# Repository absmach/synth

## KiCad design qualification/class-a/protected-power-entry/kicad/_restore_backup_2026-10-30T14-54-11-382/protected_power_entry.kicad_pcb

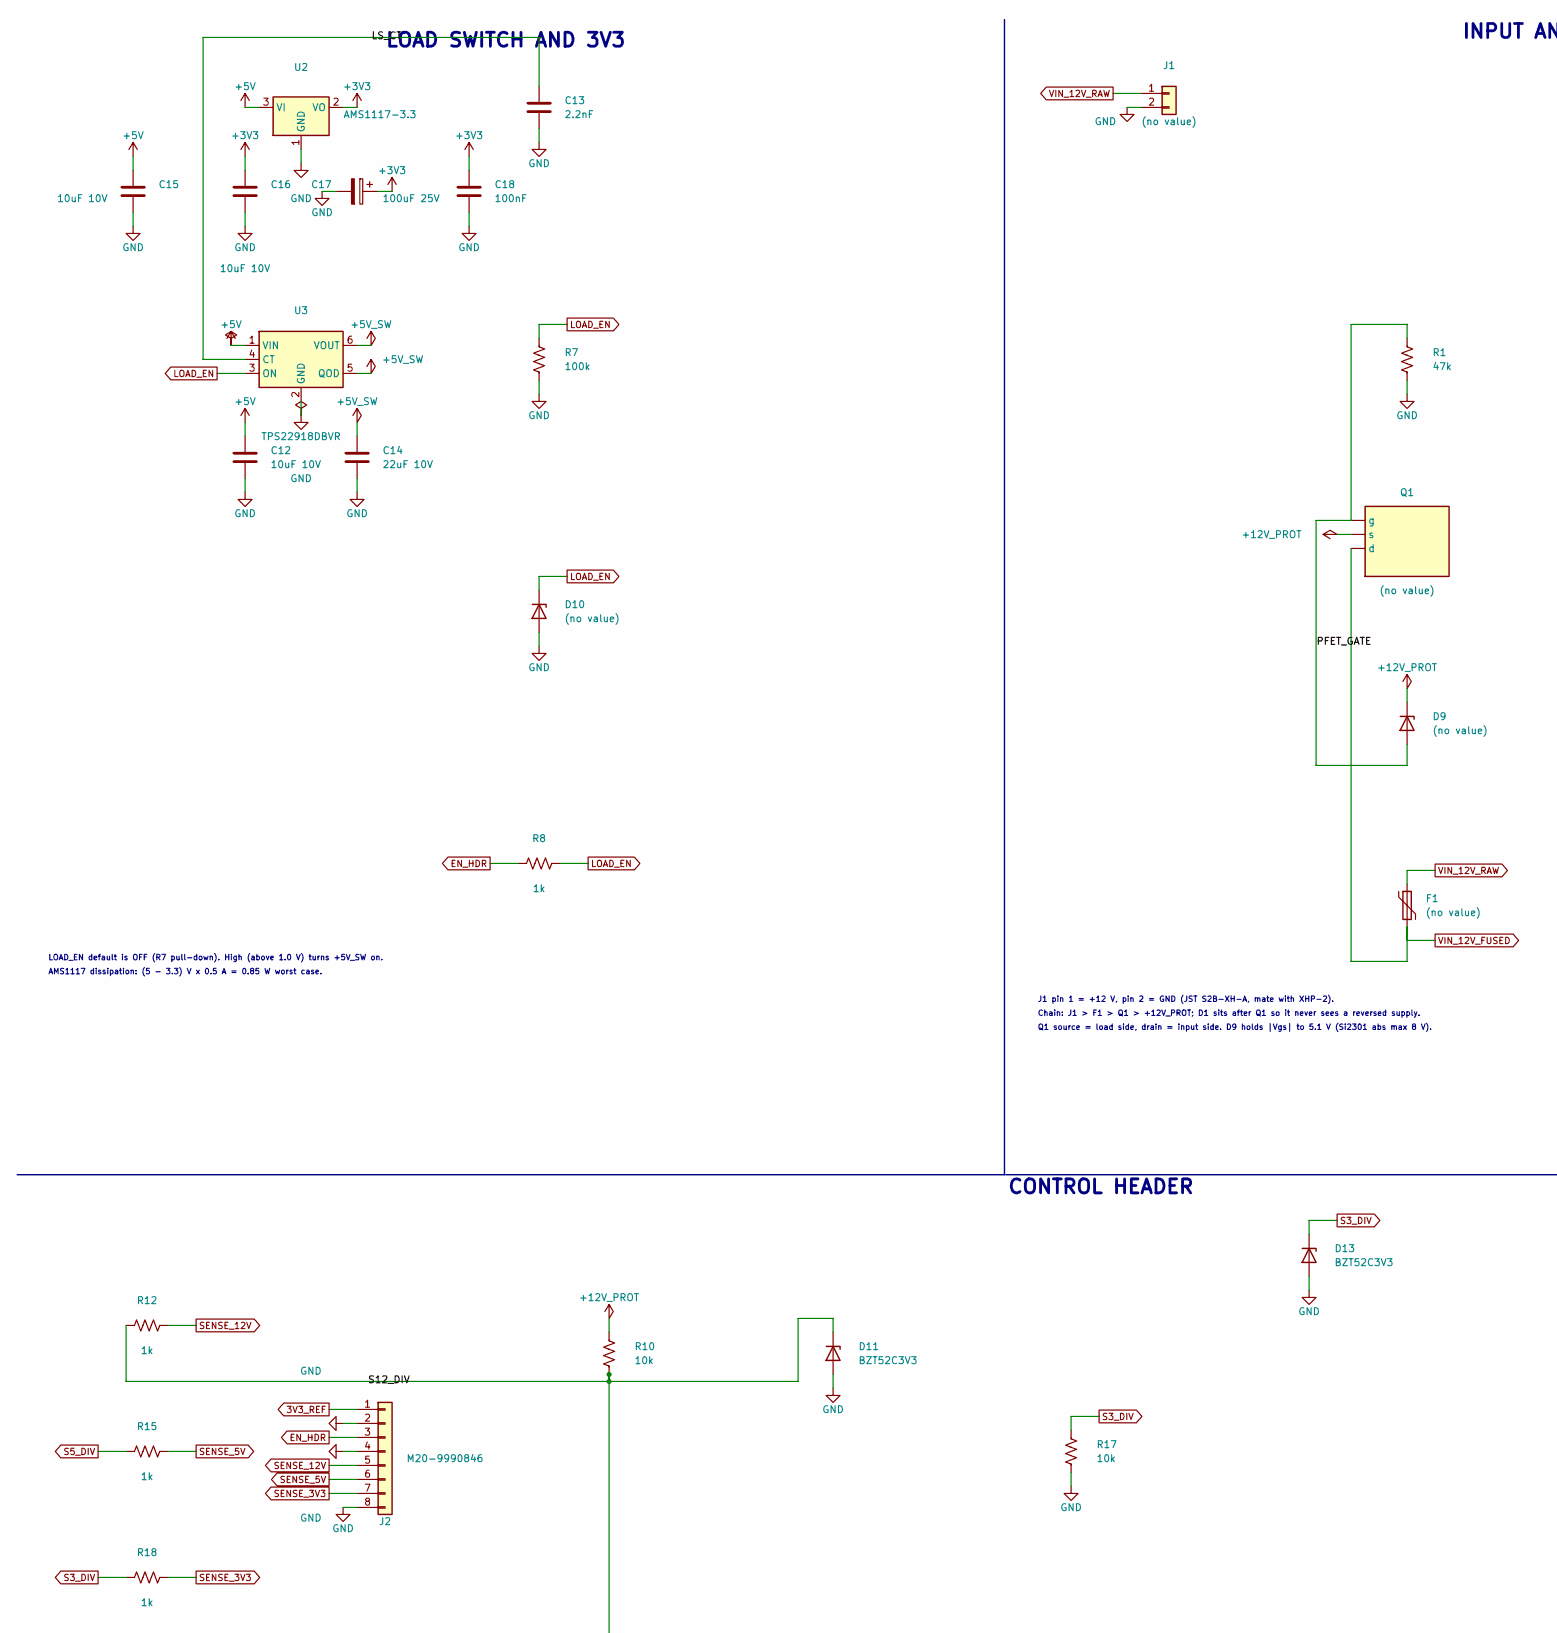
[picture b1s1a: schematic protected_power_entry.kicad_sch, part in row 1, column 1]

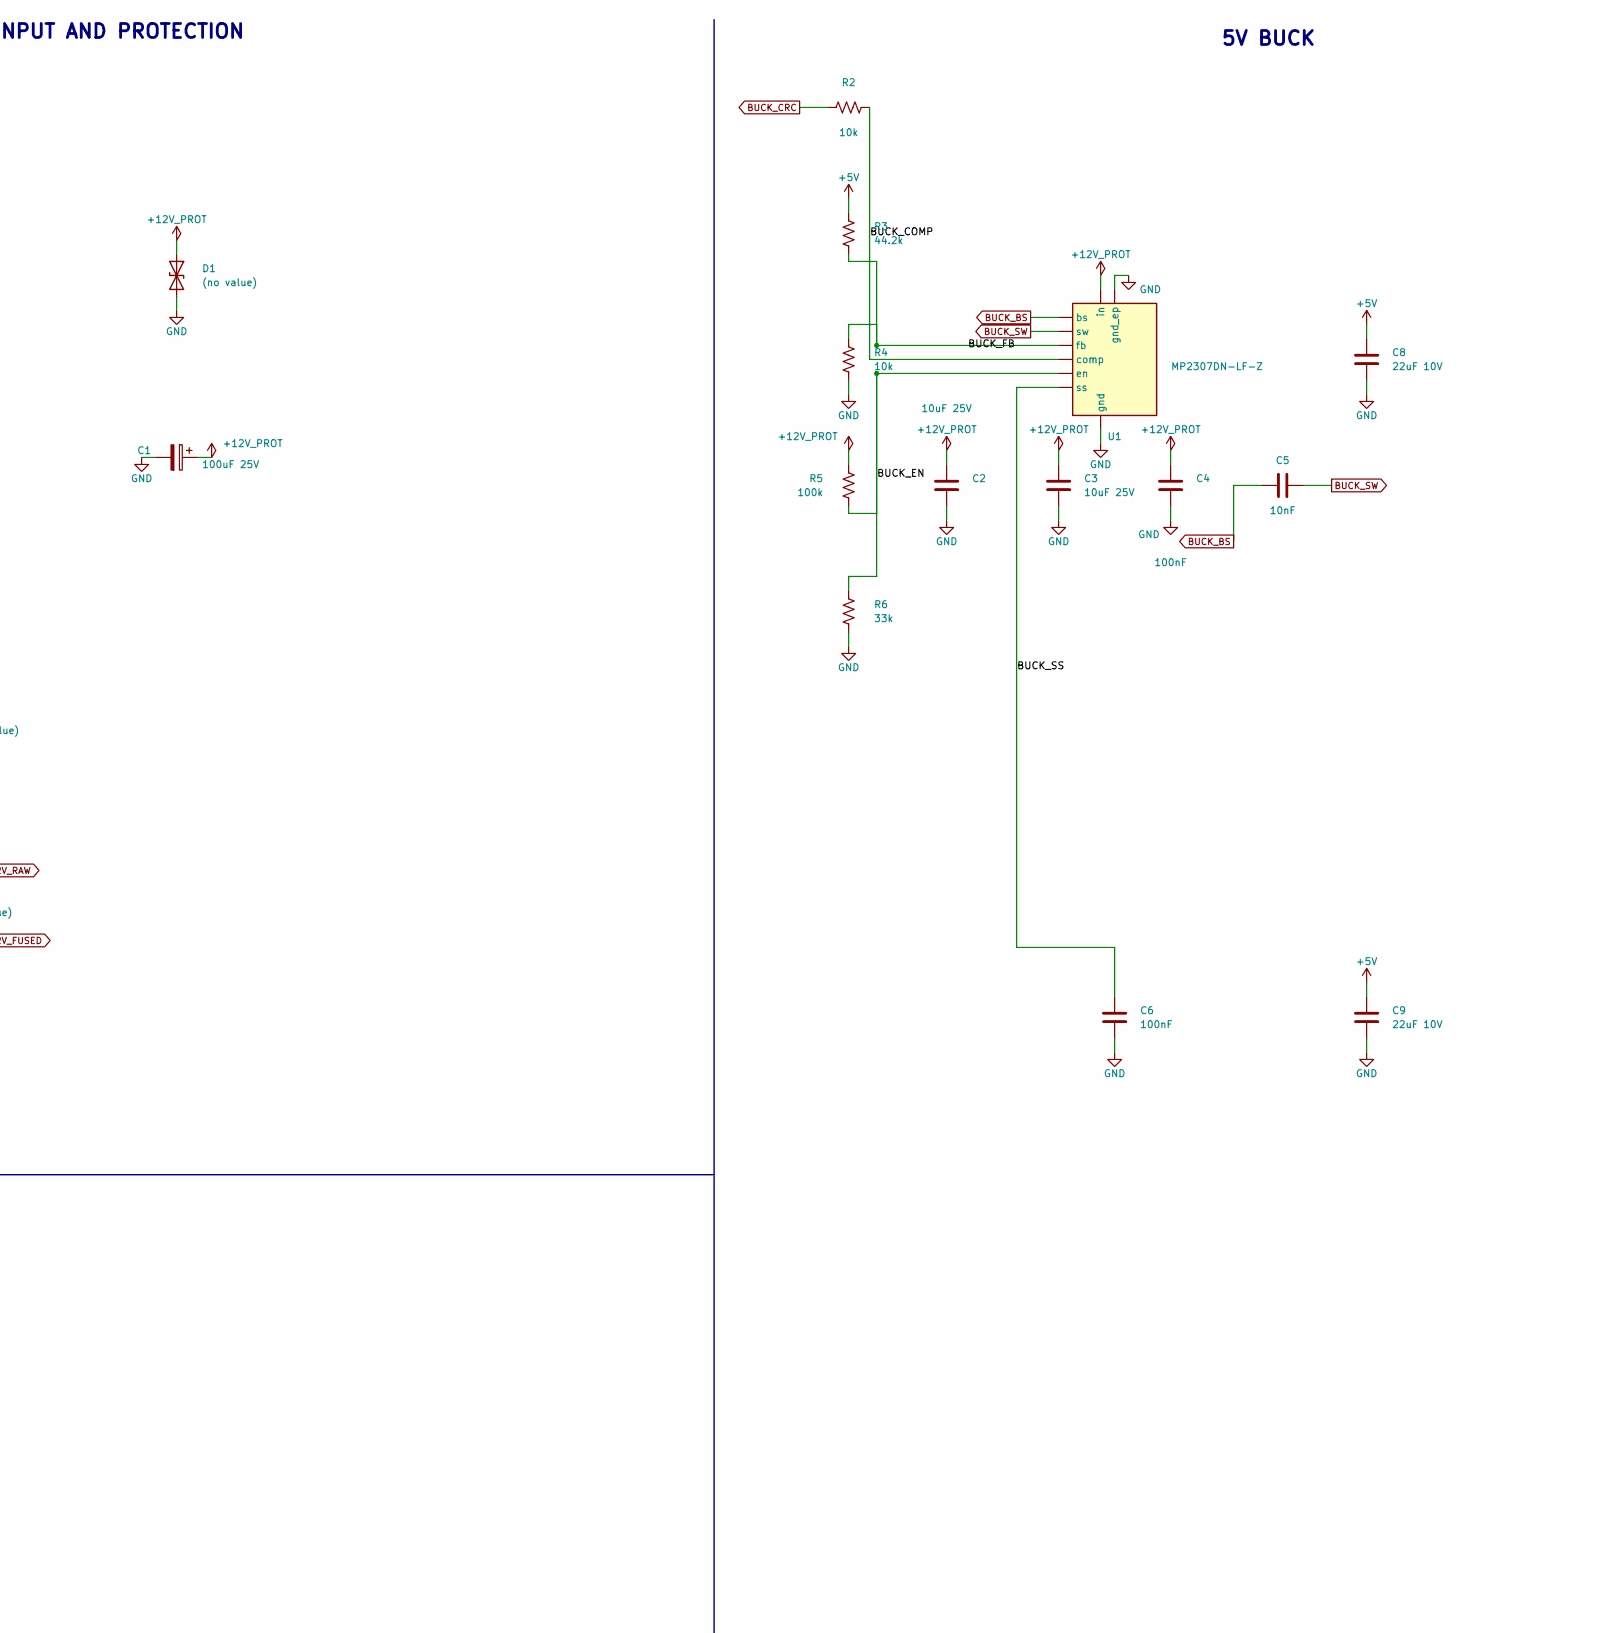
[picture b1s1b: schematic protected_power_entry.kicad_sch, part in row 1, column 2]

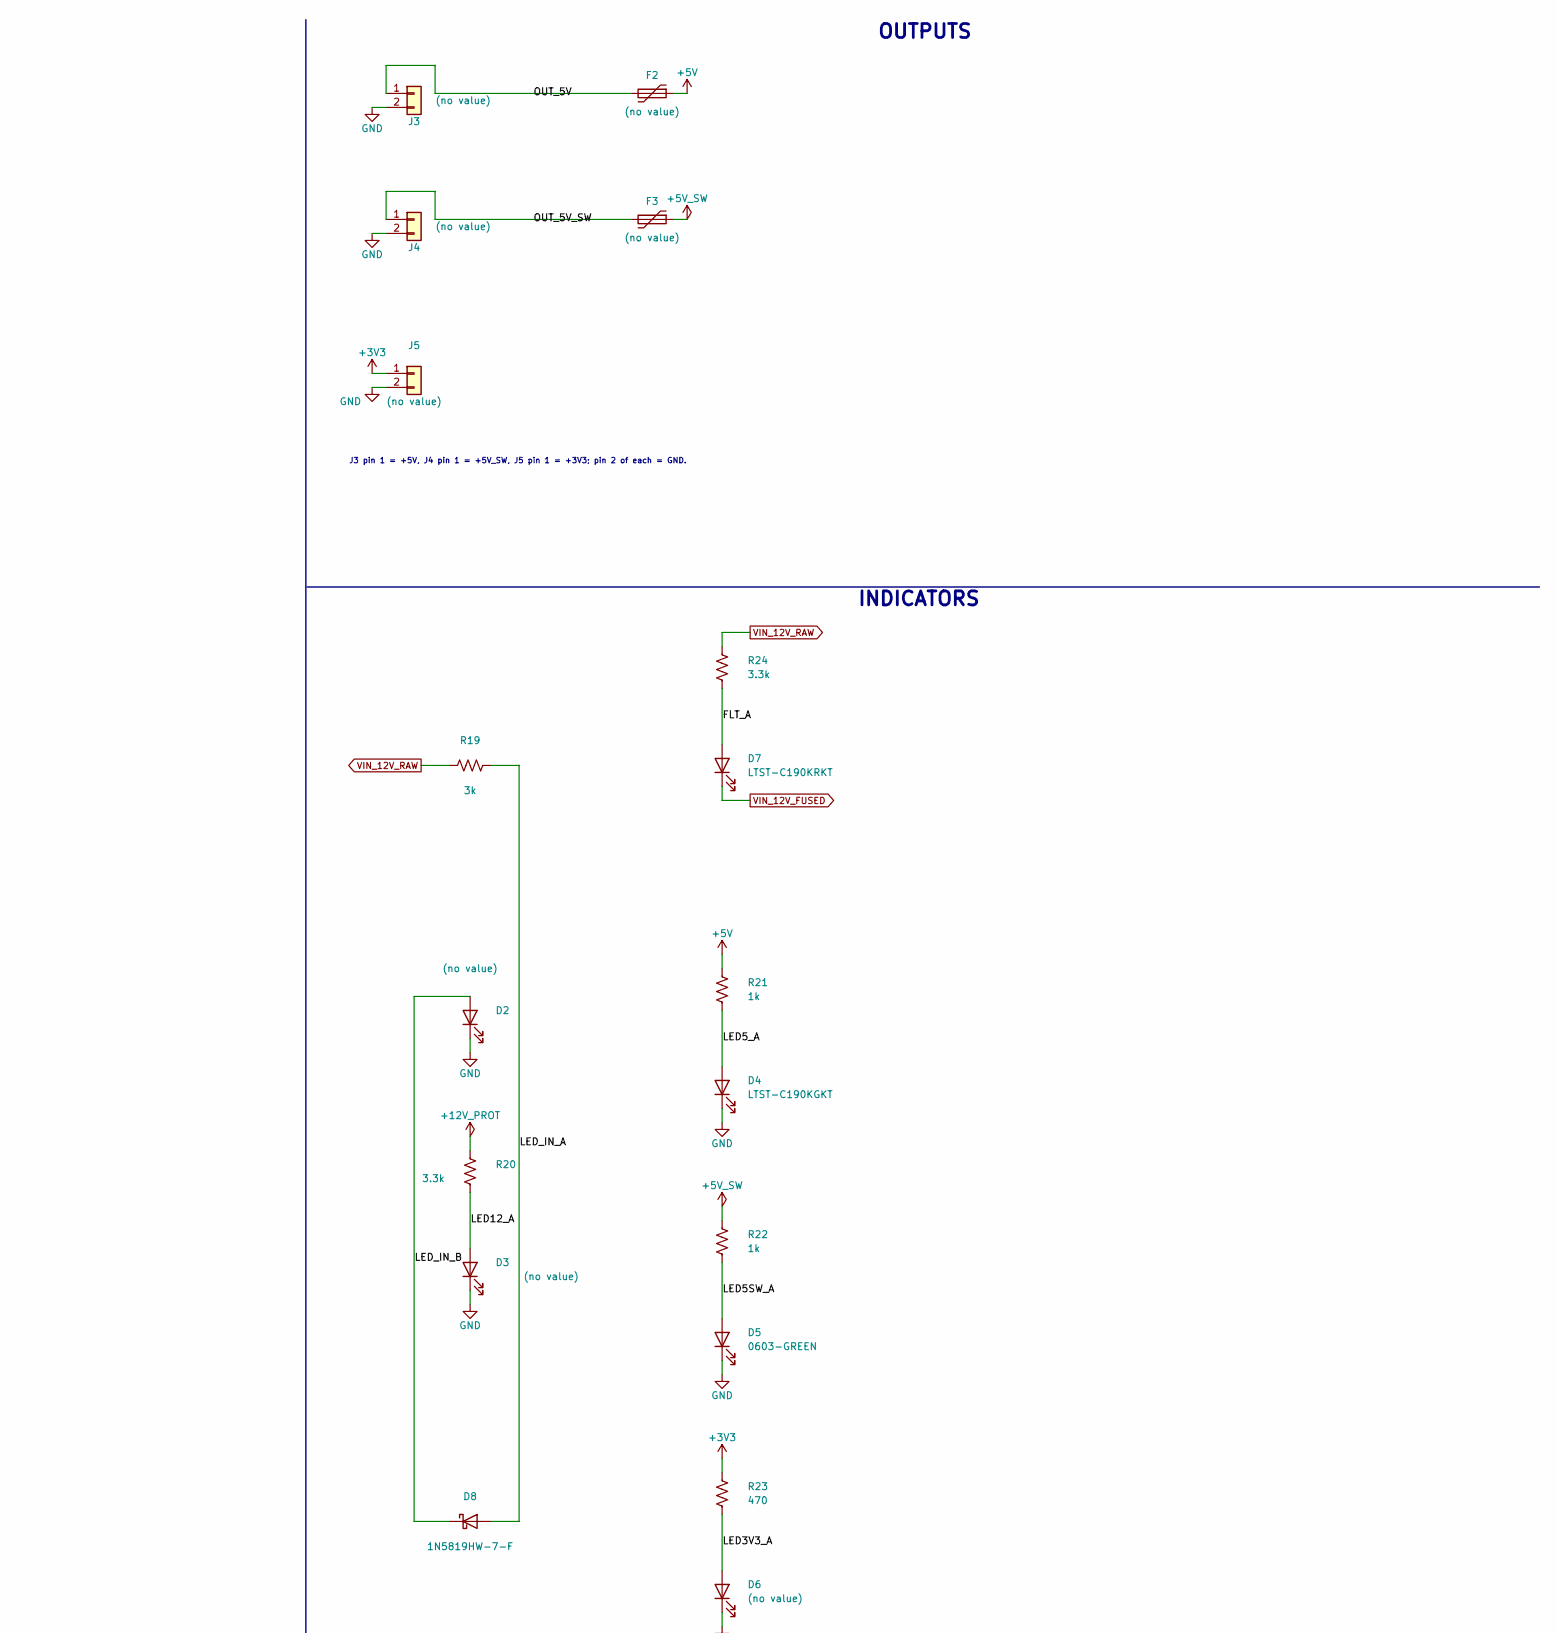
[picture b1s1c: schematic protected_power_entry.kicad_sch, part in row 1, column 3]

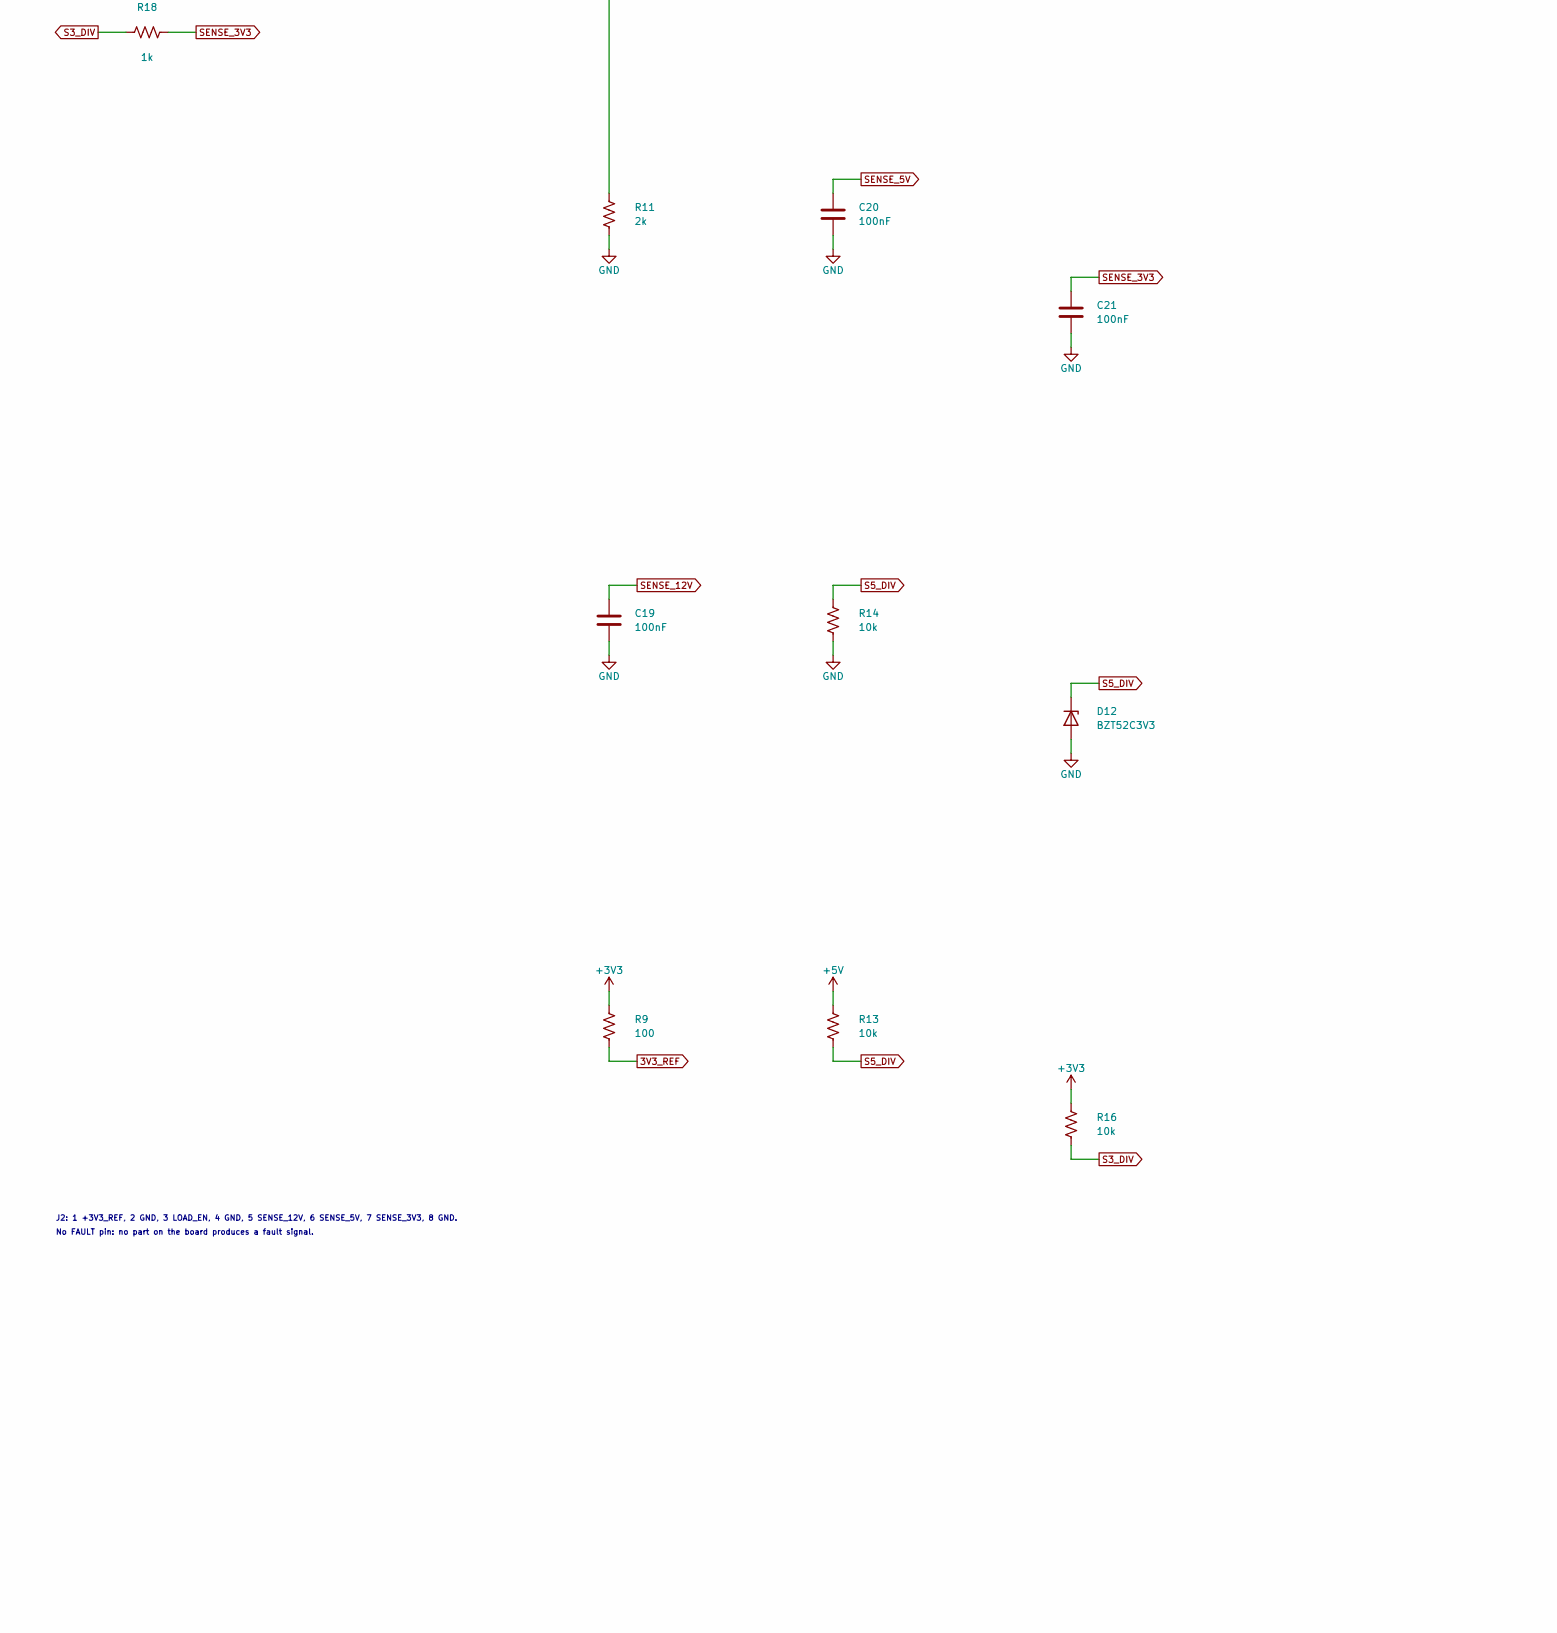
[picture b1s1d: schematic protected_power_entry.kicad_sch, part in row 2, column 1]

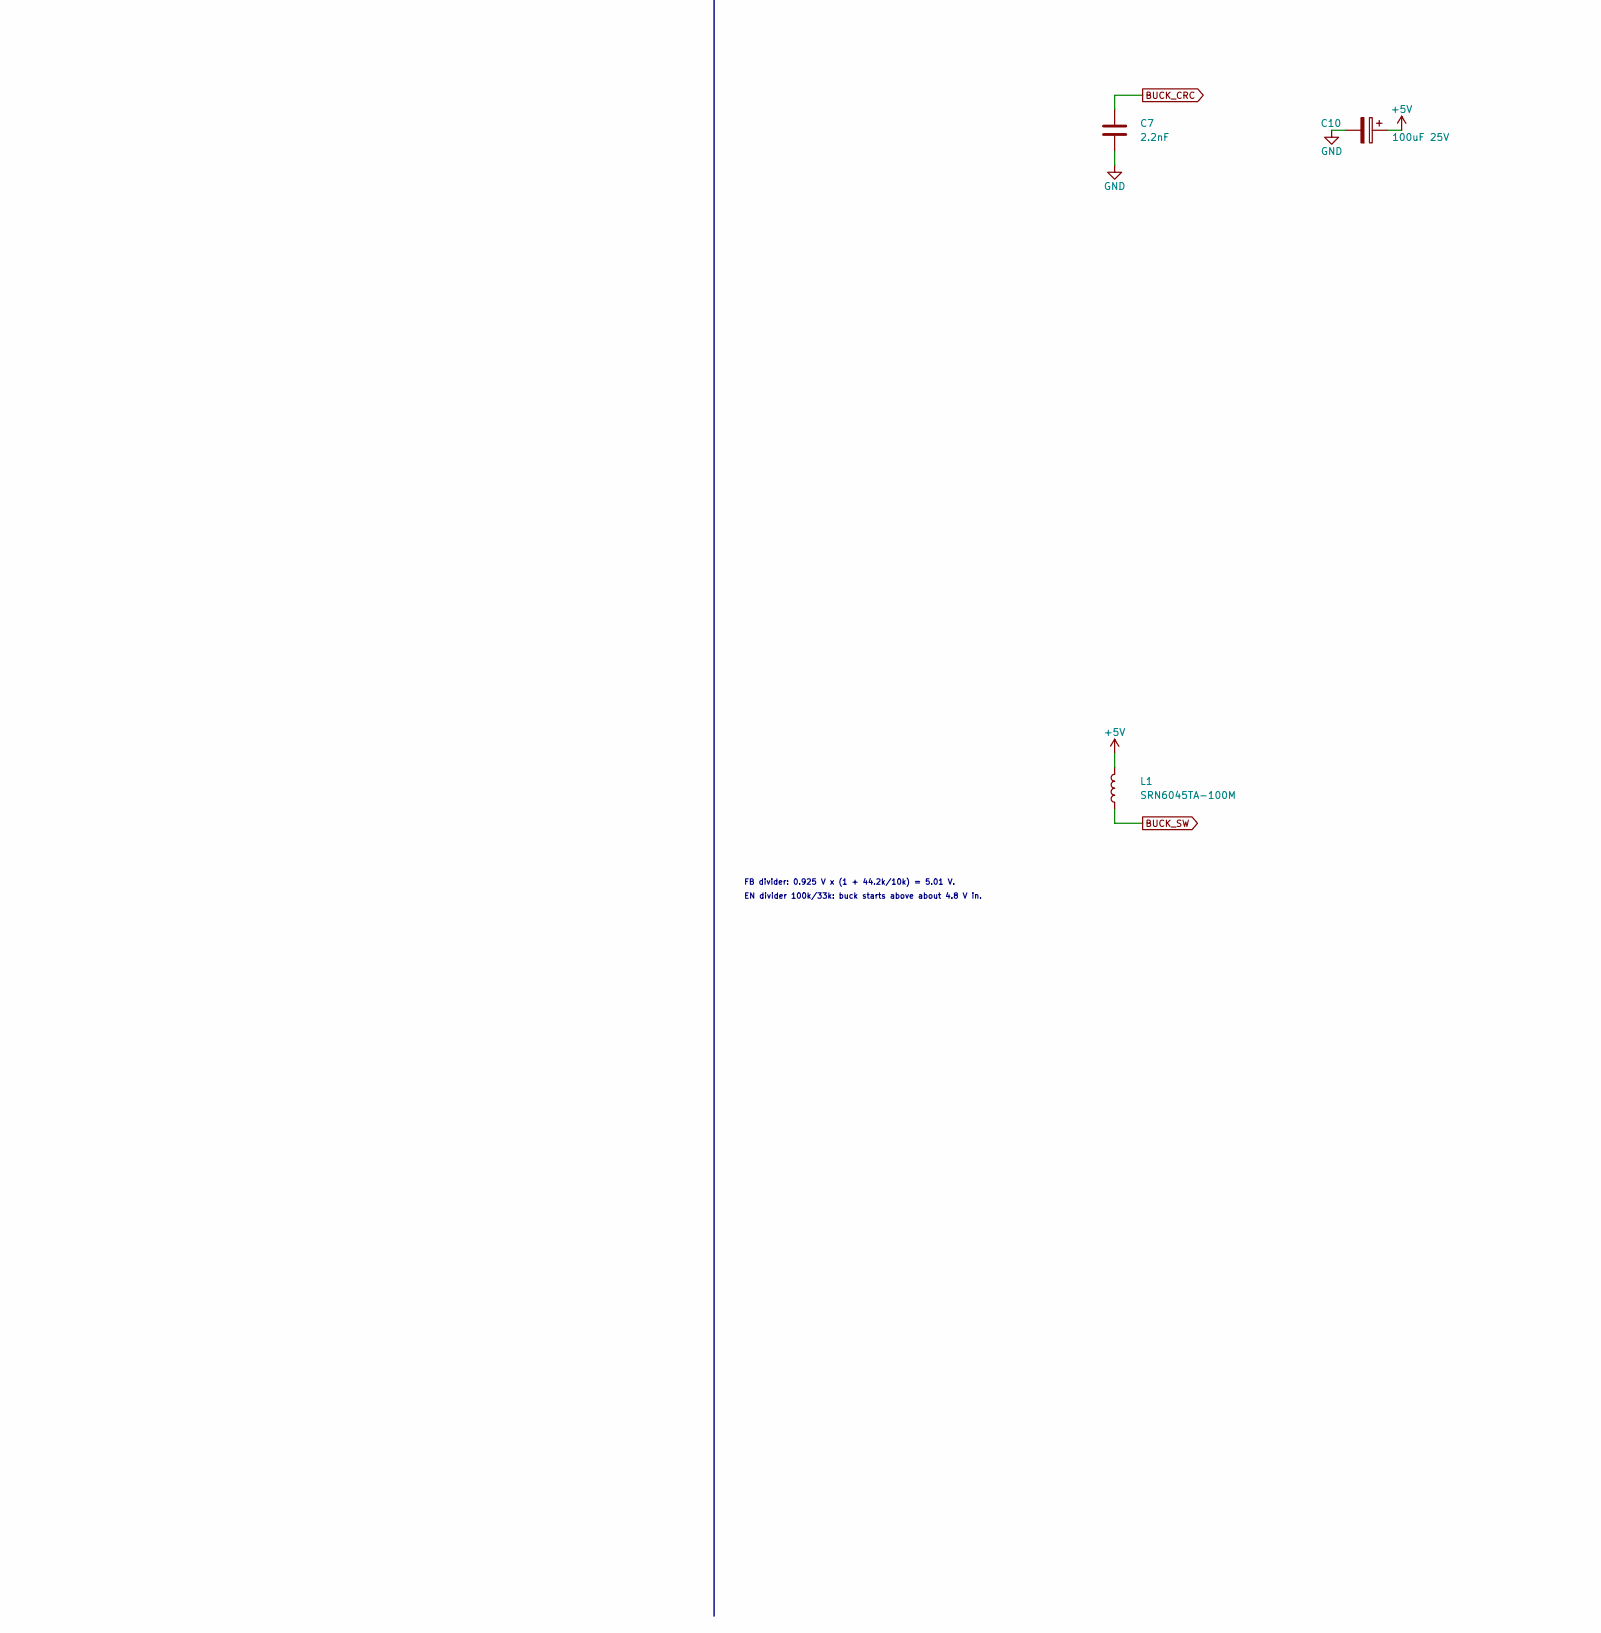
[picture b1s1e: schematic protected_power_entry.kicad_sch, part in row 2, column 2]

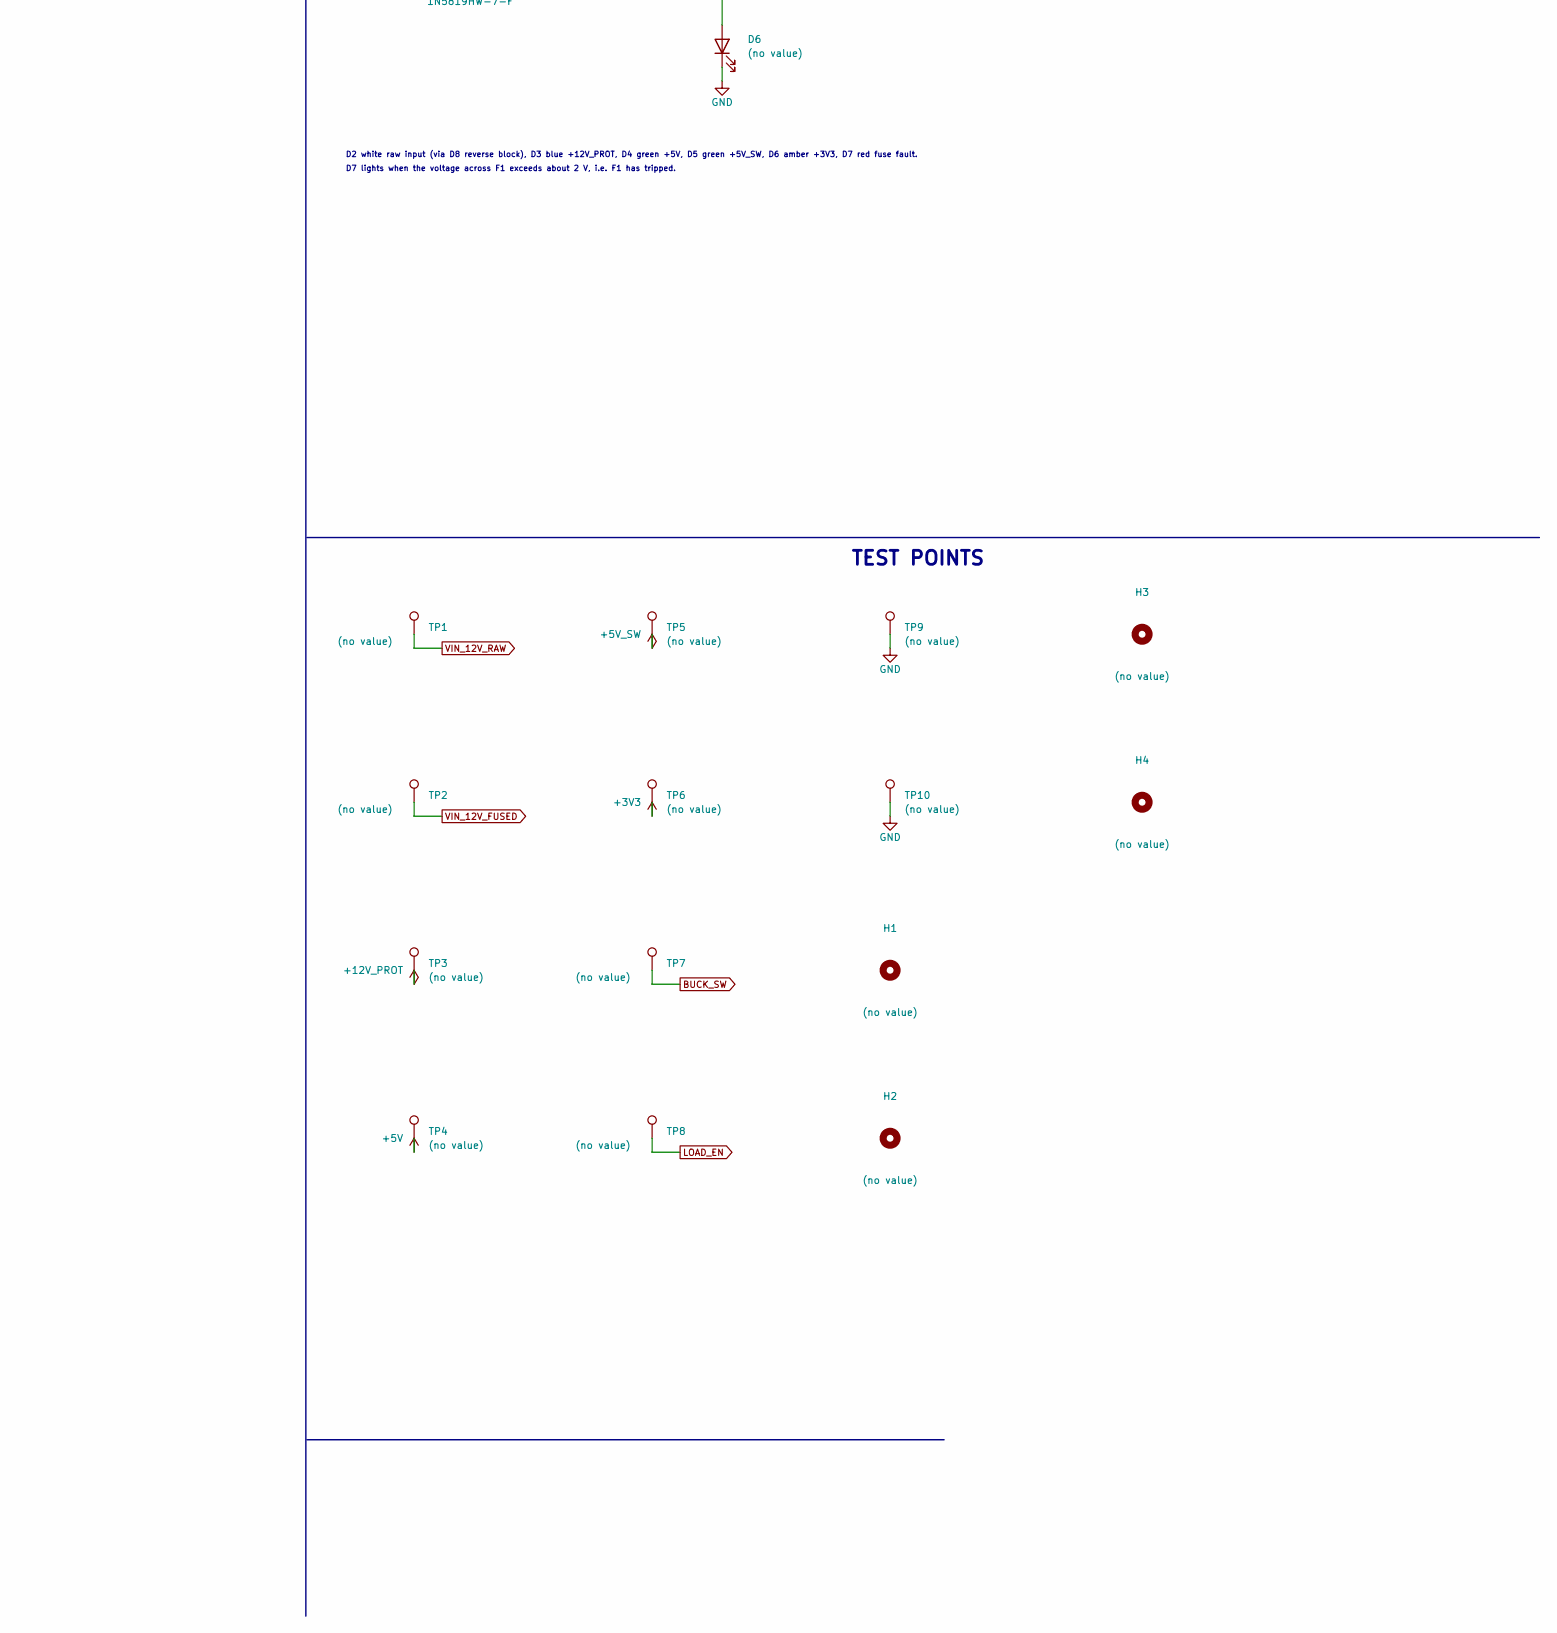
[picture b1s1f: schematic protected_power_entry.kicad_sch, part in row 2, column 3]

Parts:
C1, C10, C17: 100uF 25V; CP_Radial_D6.3mm_P2.50mm
C2, C3: 10uF 25V; C_1206_3216Metric
C4, C6, C18, C19, C20, C21: 100nF; C_0603_1608Metric
C5: 10nF; C_0603_1608Metric
C7, C13: 2.2nF; C_0603_1608Metric
C8, C9, C14: 22uF 10V; C_1206_3216Metric
C12, C15, C16: 10uF 10V; C_1206_3216Metric
D1: (no value); D_SOD-323
D2, D3, D6: (no value); LED_0603_1608Metric
D4: LTST-C190KGKT; LED_0603_1608Metric; MPN LTST-C190KGKT
D5: 0603-GREEN; LED_0603_1608Metric; MPN 0603-GREEN; LCSC C72043
D7: LTST-C190KRKT; LED_0603_1608Metric; MPN LTST-C190KRKT
D8: 1N5819HW-7-F; D_SOD-123; MPN 1N5819HW-7-F; LCSC C82544
D9, D10: (no value); D_SOD-123
D11, D12, D13: BZT52C3V3; D_SOD-123; MPN BZT52C3V3
F1, F2, F3: (no value); Fuse_Bourns_MF-RG300
H1, H2, H3, H4: (no value); MountingHole_2.5mm
J1, J3, J4, J5: (no value); JST_XH_S2B-XH-A-1_1x02_P2.50mm_Horizontal
J2: M20-9990846; PinHeader_1x08_P2.54mm_Vertical; MPN M20-9990846
L1: SRN6045TA-100M; L_Bourns_SRN6045TA; MPN SRN6045TA-100M
Q1: (no value); SOT-23
R1: 47k; R_0603_1608Metric
R2, R4, R10, R13, R14, R16, R17: 10k; R_0603_1608Metric
R3: 44.2k; R_0603_1608Metric
R5, R7: 100k; R_0603_1608Metric
R6: 33k; R_0603_1608Metric
R8, R12, R15, R18, R21, R22: 1k; R_0603_1608Metric
R9: 100; R_0603_1608Metric
R11: 2k; R_0603_1608Metric
R19: 3k; R_0603_1608Metric
R20, R24: 3.3k; R_0603_1608Metric
R23: 470; R_0603_1608Metric
TP1, TP2, TP3, TP4, TP5, TP6, TP7, TP8, TP9, TP10: (no value); TestPoint_Pad_D1.5mm
U1: MP2307DN-LF-Z; SOIC-8-1EP_3.9x4.9mm_P1.27mm_EP2.41x3.3mm; MPN MP2307DN-LF-Z; LCSC C18921
U2: AMS1117-3.3; SOT-223-3_TabPin2; MPN AMS1117-3.3; LCSC C6186
U3: TPS22918DBVR; SOT-23-6; MPN TPS22918DBVR; LCSC C131941

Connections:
3V3_REF: J2.1, R9.2
+3V3: C16.1, C17.1, C18.1, J5.1, R9.1, R16.1, R23.1, TP6.1, U2.2 (VO)
+5V: C8.1, C9.1, C10.1, C12.1, C15.1, F2.1, L1.2, R3.1, R13.1, R21.1, TP4.1, U2.3 (VI), U3.1 (VIN)
+5V_SW: C14.1, F3.1, R22.1, TP5.1, U3.5 (QOD), U3.6 (VOUT)
+12V_PROT: C1.1, C2.1, C3.1, C4.1, D1.1 (A1), D9.1 (K), Q1.2 (s), R5.1, R10.1, R20.1, TP3.1, U1.2 (in)
BUCK_BS: C5.1, U1.1 (bs)
BUCK_COMP: R2.1, U1.6 (comp)
BUCK_CRC: C7.1, R2.2
BUCK_EN: R5.2, R6.1, U1.7 (en)
BUCK_FB: R3.2, R4.1, U1.5 (fb)
BUCK_SS: C6.1, U1.8 (ss)
BUCK_SW: C5.2, L1.1, TP7.1, U1.3 (sw)
EN_HDR: J2.3, R8.1
FLT_A: D7.2 (A), R24.2
GND: C1.2, C2.2, C3.2, C4.2, C6.2, C7.2, C8.2, C9.2, C10.2, C12.2, C13.2, C14.2, C15.2, C16.2, C17.2, C18.2, C19.2, C20.2, C21.2, D1.2 (A2), D2.1 (K), D3.1 (K), D4.1 (K), D5.1 (K), D6.1 (K), D10.2 (A), D11.2 (A), D12.2 (A), D13.2 (A), J1.2, J2.2, J2.4, J2.8, J3.2, J4.2, J5.2, R1.2, R4.2, R6.2, R7.2, R11.2, R14.2, R17.2, TP9.1, TP10.1, U1.4 (gnd), U1.9 (gnd_ep), U2.1 (GND), U3.2 (GND)
LED3V3_A: D6.2 (A), R23.2
LED5SW_A: D5.2 (A), R22.2
LED5_A: D4.2 (A), R21.2
LED12_A: D3.2 (A), R20.2
LED_IN_A: D8.2 (A), R19.2
LED_IN_B: D2.2 (A), D8.1 (K)
LOAD_EN: D10.1 (K), R7.1, R8.2, TP8.1, U3.3 (ON)
LS_CT: C13.1, U3.4 (CT)
OUT_5V: F2.2, J3.1
OUT_5V_SW: F3.2, J4.1
PFET_GATE: D9.2 (A), Q1.1 (g), R1.1
S3_DIV: D13.1 (K), R16.2, R17.1, R18.1
S5_DIV: D12.1 (K), R13.2, R14.1, R15.1
S12_DIV: D11.1 (K), R10.2, R11.1, R12.1
SENSE_3V3: C21.1, J2.7, R18.2
SENSE_5V: C20.1, J2.6, R15.2
SENSE_12V: C19.1, J2.5, R12.2
VIN_12V_FUSED: D7.1 (K), F1.2, Q1.3 (d), TP2.1
VIN_12V_RAW: F1.1, J1.1, R19.1, R24.1, TP1.1

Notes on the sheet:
INPUT AND PROTECTION
5V BUCK
LOAD SWITCH AND 3V3
OUTPUTS
CONTROL HEADER
INDICATORS
TEST POINTS
J1 pin 1 = +12 V, pin 2 = GND (JST S2B-XH-A, mate with XHP-2).
Chain: J1 > F1 > Q1 > +12V_PROT; D1 sits after Q1 so it never sees a reversed supply.
Q1 source = load side, drain = input side. D9 holds |Vgs| to 5.1 V (Si2301 abs max 8 V).
FB divider: 0.925 V x (1 + 44.2k/10k) = 5.01 V.
EN divider 100k/33k: buck starts above about 4.8 V in.
LOAD_EN default is OFF (R7 pull-down). High (above 1.0 V) turns +5V_SW on.
AMS1117 dissipation: (5 - 3.3) V x 0.5 A = 0.85 W worst case.
J3 pin 1 = +5V, J4 pin 1 = +5V_SW, J5 pin 1 = +3V3; pin 2 of each = GND.
J2: 1 +3V3_REF, 2 GND, 3 LOAD_EN, 4 GND, 5 SENSE_12V, 6 SENSE_5V, 7 SENSE_3V3, 8 GND.
No FAULT pin: no part on the board produces a fault signal.
D2 white raw input (via D8 reverse block), D3 blue +12V_PROT, D4 green +5V, D5 green +5V_SW, D6 amber +3V3, D7 red fuse fault.
D7 lights when the voltage across F1 exceeds about 2 V, i.e. F1 has tripped.
